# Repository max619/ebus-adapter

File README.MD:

# ebus-adapter

Schematics for EBus adapter

Enclosure D2MG

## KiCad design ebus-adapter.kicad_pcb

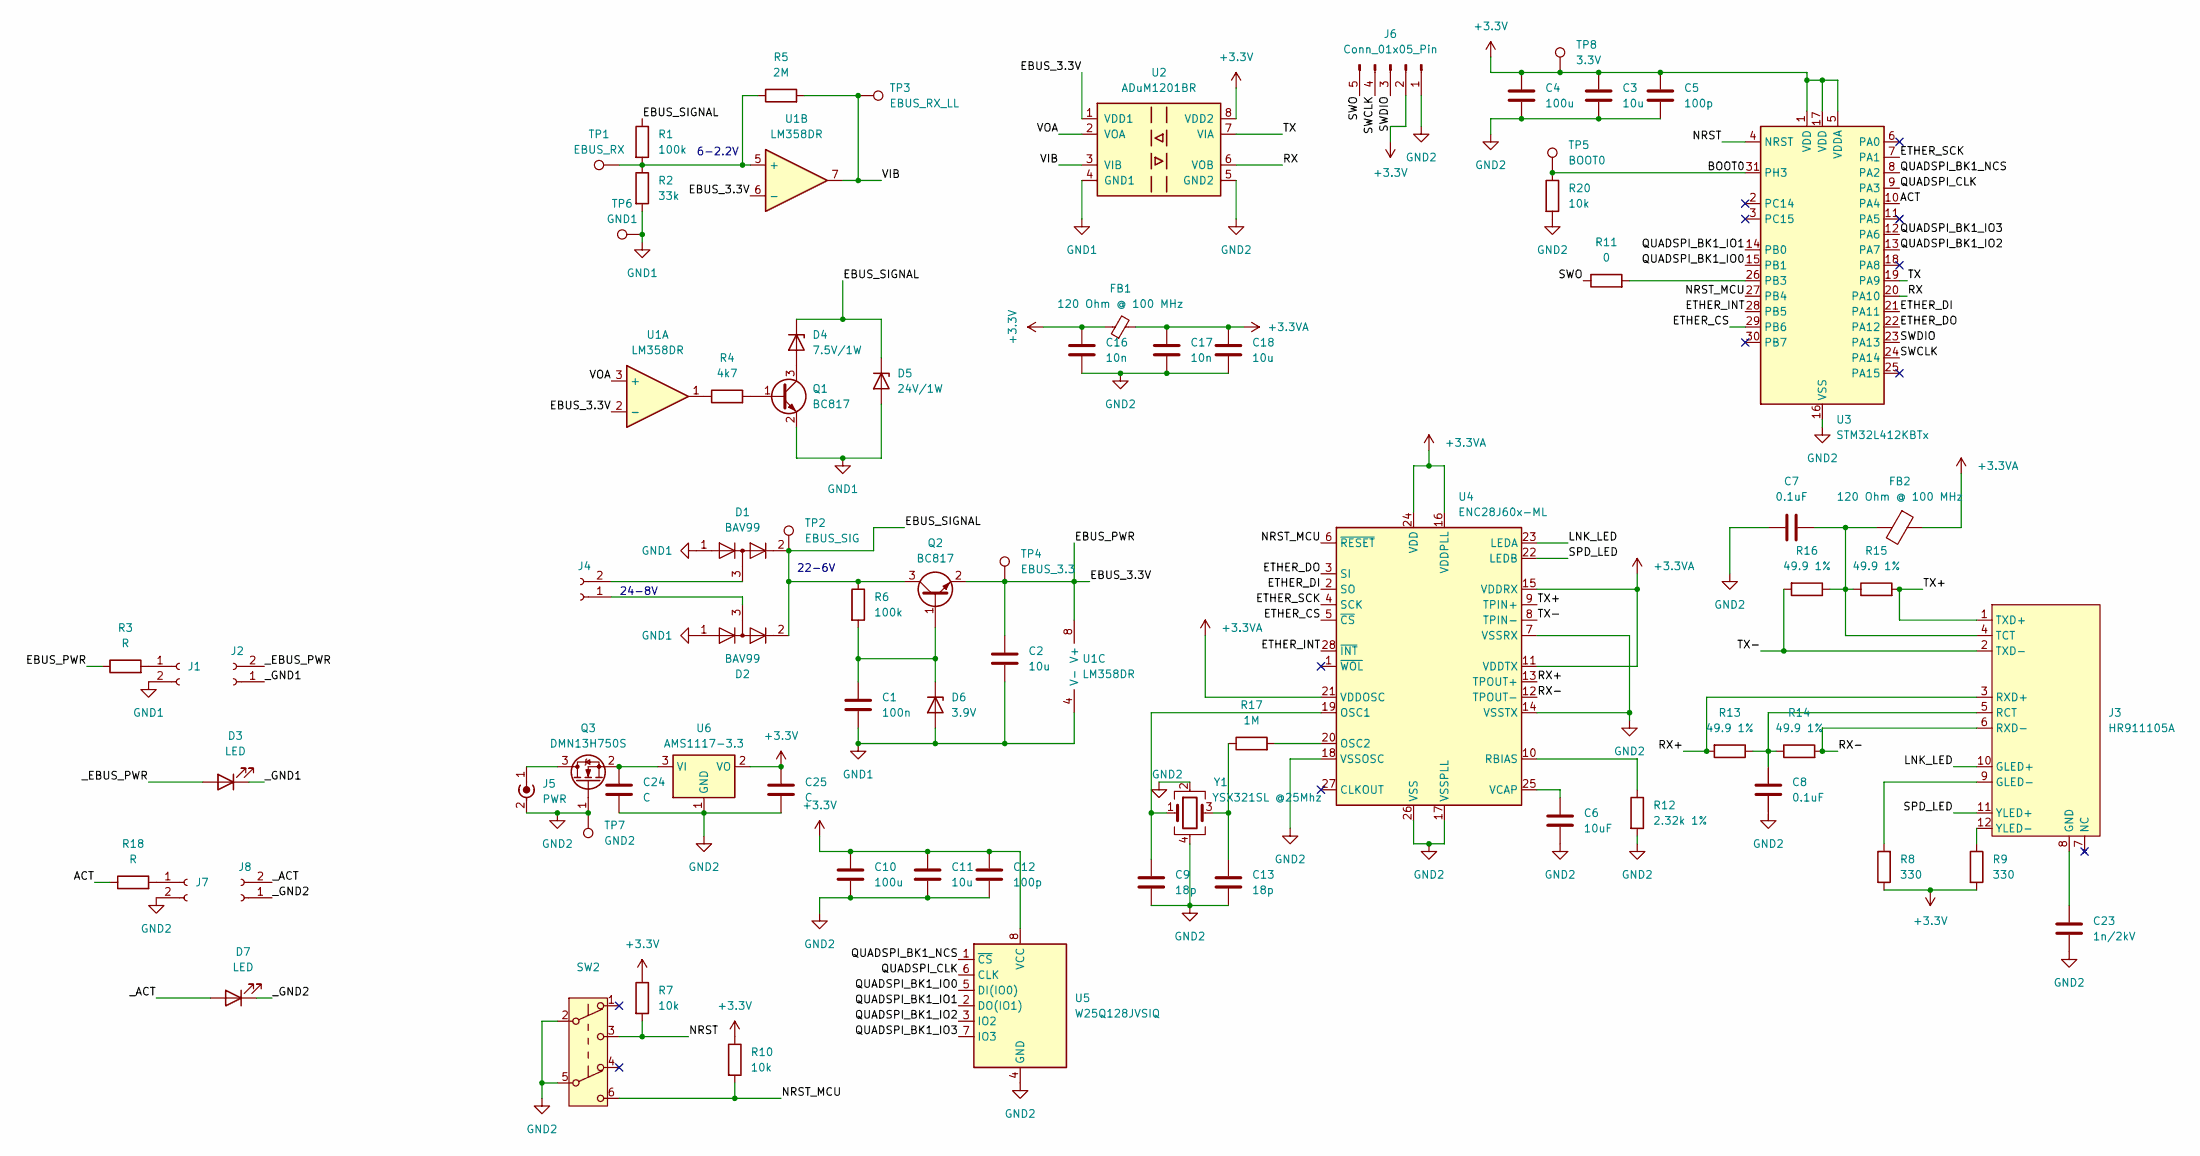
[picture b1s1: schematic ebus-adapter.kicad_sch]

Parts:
C1: 100n; C_0603_1608Metric_Pad1.08x0.95mm_HandSolder
C2, C3, C11, C18: 10u; C_0603_1608Metric_Pad1.08x0.95mm_HandSolder
C4, C10: 100u; C_0603_1608Metric_Pad1.08x0.95mm_HandSolder
C5, C12: 100p; C_0603_1608Metric_Pad1.08x0.95mm_HandSolder
C6: 10uF; C_0603_1608Metric_Pad1.08x0.95mm_HandSolder
C7, C8: 0.1uF; C_0603_1608Metric_Pad1.08x0.95mm_HandSolder
C9, C13: 18p; C_0603_1608Metric_Pad1.08x0.95mm_HandSolder
C16, C17: 10n; C_0603_1608Metric_Pad1.08x0.95mm_HandSolder
C23: 1n/2kV; C_0603_1608Metric_Pad1.08x0.95mm_HandSolder
C24, C25: C; C_0603_1608Metric_Pad1.08x0.95mm_HandSolder
D1, D2: BAV99; SOT-23
D3, D7: LED; LED_D1.8mm_W3.3mm_H2.4mm
D4: 7.5V/1W; D_SOD-123; Part Name LMSZ5228BT1G
D5: 24V/1W; D_SOD-123; Part Name LMSZ5228BT1G
D6: 3.9V; D_SOD-123; Part Name LMSZ5228BT1G
FB1, FB2: 120 Ohm @ 100 MHz; R_1206_3216Metric_Pad1.30x1.75mm_HandSolder; Part Name YI321611Z121-6R0T
J1, J2, J7, J8: Conn_01x02_Socket; Molex_PicoBlade_53047-0210_1x02_P1.25mm_Vertical
J3: HR911105A; Part Name HR911105A
J4: WJ2EDGRC-5.08-2P; WJ2EDGRC; Part Name WJ2EDGRC-5.08-2P
J5: PWR; WJ2EDGRC; Part Name WJ2EDGRC-5.08-2P
J6: Conn_01x05_Pin; PinHeader_1x05_P2.54mm_Vertical
Q1, Q2: BC817; SOT-23
Q3: DMN13H750S; SOT-23; Part Name DMN13H750S-7
R1, R6: 100k; R_0603_1608Metric_Pad0.98x0.95mm_HandSolder
R2: 33k; R_0603_1608Metric_Pad0.98x0.95mm_HandSolder
R3, R18: R; R_0603_1608Metric_Pad0.98x0.95mm_HandSolder
R4: 4k7; R_0603_1608Metric_Pad0.98x0.95mm_HandSolder
R5: 2M; R_0603_1608Metric_Pad0.98x0.95mm_HandSolder
R7, R10, R20: 10k; R_0603_1608Metric_Pad0.98x0.95mm_HandSolder
R8, R9: 330; R_0603_1608Metric_Pad0.98x0.95mm_HandSolder
R11: 0; R_0603_1608Metric_Pad0.98x0.95mm_HandSolder
R12: 2.32k 1%; R_0603_1608Metric_Pad0.98x0.95mm_HandSolder
R13, R14, R15, R16: 49.9 1%; R_0603_1608Metric_Pad0.98x0.95mm_HandSolder
R17: 1M; R_0603_1608Metric_Pad0.98x0.95mm_HandSolder
SW2: PS-7054SVB-6PN; PS-7054SVB; Part Name PS-7054SVB-6PN
TP1: EBUS_RX; TestPoint_THTPad_1.5x1.5mm_Drill0.7mm
TP2: EBUS_SIG; TestPoint_THTPad_1.5x1.5mm_Drill0.7mm
TP3: EBUS_RX_LL; TestPoint_THTPad_1.5x1.5mm_Drill0.7mm
TP4: EBUS_3.3; TestPoint_THTPad_1.5x1.5mm_Drill0.7mm
TP5: BOOT0; TestPoint_THTPad_1.5x1.5mm_Drill0.7mm
TP6: GND1; TestPoint_THTPad_1.5x1.5mm_Drill0.7mm
TP7: GND2; TestPoint_THTPad_1.5x1.5mm_Drill0.7mm
TP8: 3.3V; TestPoint_THTPad_1.5x1.5mm_Drill0.7mm
U1: LM358DR; SOIC-8_3.9x4.9mm_P1.27mm; Part Name LM358DR
U2: ADuM1201BR; SOIC-8_3.9x4.9mm_P1.27mm
U3: STM32L412KBTx; LQFP-32_7x7mm_P0.8mm; Part Number C529438
U4: ENC28J60x-ML; QFN-28-1EP_6x6mm_P0.65mm_EP4.25x4.25mm
U5: W25Q128JVSIQ; SOIC-8_5.23x5.23mm_P1.27mm; Part Name W25Q128JVSIQ
U6: AMS1117-3.3; SOT-223-3_TabPin2; Part Number C5250992
Y1: YSX321SL @25Mhz; YSX321SL; Part Name XL2EL89COI-111YLC-25M

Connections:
+3.3V: C3.1, C4.1, C5.1, C10.1, C11.1, C12.1, C16.1, C25.1, FB1.1, J6.2, R7.1, R8.1, R9.2, R10.1, TP8.1, U2.8 (VDD2), U3.1 (VDD), U3.5 (VDDA), U3.17 (VDD), U5.8 (VCC), U6.2 (VO)
+3.3VA: C17.1, C18.1, FB1.2, FB2.1, U4.11 (VDDTX), U4.15 (VDDRX), U4.16 (VDDPLL), U4.21 (VDDOSC), U4.24 (VDD)
/ACT: R18.1, U3.10 (PA4)
/BOOT0: R20.1, TP5.1, U3.31 (PH3)
/EBUS_3.3V: C2.1, Q2.2 (E), R3.1, TP4.1, U1.2 (-), U1.6 (-), U1.8 (V+), U2.1 (VDD1)
/EBUS_SIGNAL: D1.2 (A), D2.2 (A), D4.1 (K), D5.1 (K), Q2.3 (C), R1.1, R6.1, TP2.1
/ETHER_CS: U3.29 (PB6), U4.5 (~CS)
/ETHER_DI: U3.21 (PA11), U4.2 (SO)
/ETHER_DO: U3.22 (PA12), U4.3 (SI)
/ETHER_INT: U3.28 (PB5), U4.28 (~INT)
/ETHER_SCK: U3.7 (PA1), U4.4 (SCK)
/LNK_LED: J3.10 (GLED+), U4.23 (LEDA)
/NRST: R7.2, SW2.3 (C), U3.4 (NRST)
/NRST_MCU: R10.2, SW2.6 (C), U3.27 (PB4), U4.6 (~RESET)
/QUADSPI_BK1_IO0: U3.15 (PB1), U5.5 (DI(IO0))
/QUADSPI_BK1_IO1: U3.14 (PB0), U5.2 (DO(IO1))
/QUADSPI_BK1_IO2: U3.13 (PA7), U5.3 (IO2)
/QUADSPI_BK1_IO3: U3.12 (PA6), U5.7 (IO3)
/QUADSPI_BK1_NCS: U3.8 (PA2), U5.1 (~CS)
/QUADSPI_CLK: U3.9 (PA3), U5.6 (CLK)
/RX: U2.6 (VOB), U3.20 (PA10)
/RX+: J3.3 (RXD+), R13.2, U4.13 (TPOUT+)
/RX-: J3.6 (RXD-), R14.2, U4.12 (TPOUT-)
/SPD_LED: J3.11 (YLED+), U4.22 (LEDB)
/SWCLK: J6.4, U3.24 (PA14)
/SWDIO: J6.3, U3.23 (PA13)
/SWO: J6.5, R11.1
/TX: U2.7 (VIA), U3.19 (PA9)
/TX+: J3.1 (TXD+), R15.2, U4.9 (TPIN+)
/TX-: J3.2 (TXD-), R16.2, U4.8 (TPIN-)
/VIB: R5.2, TP3.1, U1.7, U2.3 (VIB)
/VOA: U1.3 (+), U2.2 (VOA)
/_ACT: D7.2 (A), J8.2
/_EBUS_PWR: D3.2 (A), J2.2
/_GND1: D3.1 (K), J2.1
/_GND2: D7.1 (K), J8.1
GND1: C1.2, C2.2, D1.1 (K), D2.1 (K), D5.2 (A), D6.2 (A), J1.2, Q1.2 (E), R2.2, TP6.1, U1.4 (V-), U2.4 (GND1)
GND2: C3.2, C4.2, C5.2, C6.2, C7.1, C8.1, C9.2, C10.2, C11.2, C12.2, C13.2, C16.2, C17.2, C18.2, C23.2, C24.2, C25.2, J5.2 (Ext), J6.1, J7.2, Q3.1 (G), R12.2, R20.2, SW2.2 (B), SW2.5 (B), TP7.1, U2.5 (GND2), U3.16 (VSS), U3.32 (VSS), U4.7 (VSSRX), U4.14 (VSSTX), U4.17 (VSSPLL), U4.18 (VSSOSC), U4.26 (VSS), U5.4 (GND), U6.1 (GND), Y1.2, Y1.4
unnamed: C13.1, R17.1, Y1.3
unnamed: D4.2 (A), Q1.3 (C)
unnamed: C1.1, D6.1 (K), Q2.1 (B), R6.2
unnamed: J1.1, R3.2
unnamed: J3.9 (GLED-), R8.2
unnamed: C23.1, J3.8 (GND)
unnamed: C8.2, J3.5 (RCT), R13.1, R14.1
unnamed: C7.2, FB2.2, J3.4 (TCT), R15.1, R16.1
unnamed: J3.12 (YLED-), R9.1
unnamed: D2.3 (K), J4.1
unnamed: D1.3 (K), J4.2
unnamed: J5.1 (In), Q3.3 (D)
unnamed: J7.1, R18.2
unnamed: Q1.1 (B), R4.2
unnamed: C24.1, Q3.2 (S), U6.3 (VI)
unnamed: R4.1, U1.1
unnamed: R1.2, R2.1, R5.1, TP1.1, U1.5 (+)
unnamed: R11.2, U3.26 (PB3)
unnamed: C9.1, U4.19 (OSC1), Y1.1
unnamed: R17.2, U4.20 (OSC2)
unnamed: R12.1, U4.10 (RBIAS)
unnamed: C6.1, U4.25 (VCAP)

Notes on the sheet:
22-6V
6-2.2V
24-8V

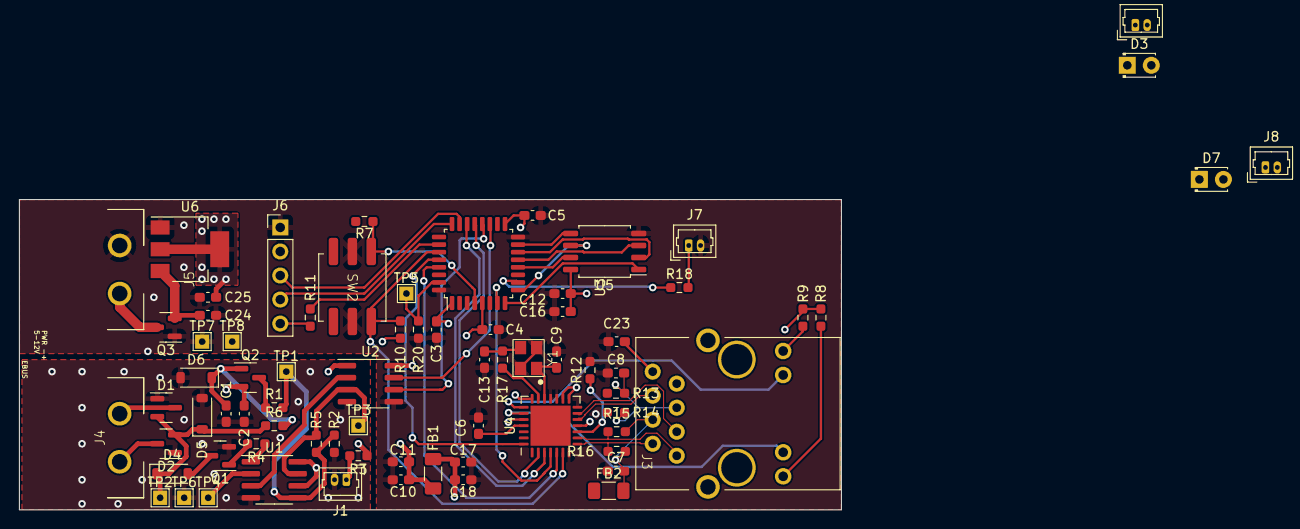
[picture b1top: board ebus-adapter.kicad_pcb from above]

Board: 4 copper layers, 86.9 x 32.8 mm, 74 parts (0 on the bottom side), 60 nets.

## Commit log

2024-01-02 Added EBus to UART converter
2024-01-05 Updated adapter added SPI 2 Etherenet adapter
2024-06-16 Updated schematics and pcb
